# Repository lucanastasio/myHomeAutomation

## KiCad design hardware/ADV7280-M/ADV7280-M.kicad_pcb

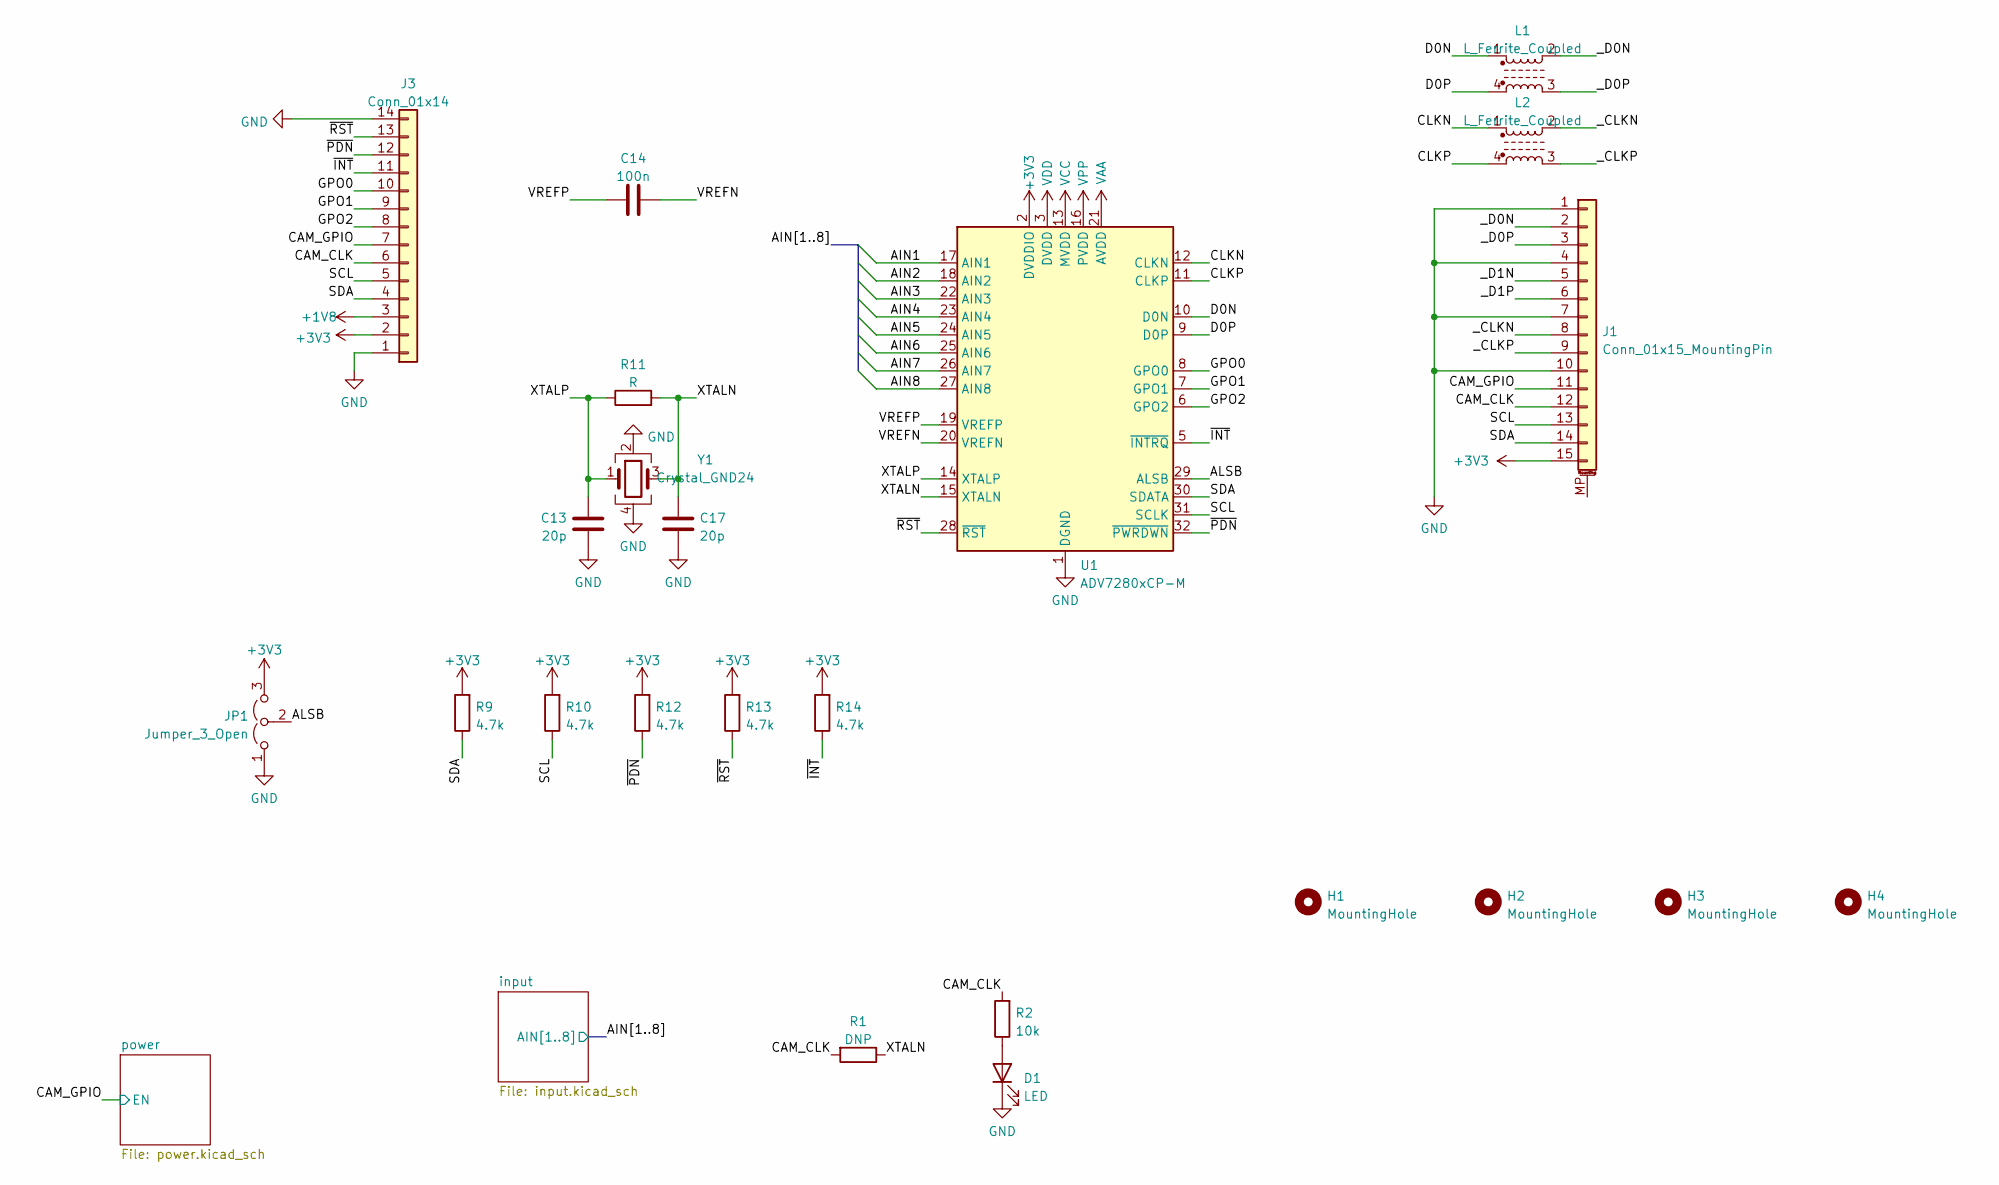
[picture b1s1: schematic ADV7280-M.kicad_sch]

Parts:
C13, C17: 20p; C_0402_1005Metric
C14: 100n; C_0402_1005Metric
D1: LED; LED_0603_1608Metric
H1, H2, H3, H4: MountingHole; MountingHole_2.7mm_M2.5
J1: Conn_01x15_MountingPin; TE_1-84952-5_1x15-1MP_P1.0mm_Horizontal
J3: Conn_01x14; PinHeader_1x14_P2.54mm_Vertical
JP1: Jumper_3_Open; PinHeader_1x03_P2.54mm_Vertical
L1, L2: L_Ferrite_Coupled; L_CommonModeChoke_Coilcraft_0603USB
R1: DNP; R_0603_1608Metric
R2: 10k; R_0603_1608Metric
R9, R10, R12, R13, R14: 4.7k; R_0603_1608Metric
R11: R; R_0402_1005Metric
U1: ADV7280xCP-M; LFCSP-32-1EP_5x5mm_P0.5mm_EP3.6x3.6mm
Y1: Crystal_GND24; Crystal_SMD_3225-4Pin_3.2x2.5mm

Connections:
+1V8: J3.3; also elsewhere on the board
+3V3: J1.15, J3.2, JP1.3 (B), R9.2, R10.2, R12.2, R13.2, R14.2, U1.2 (DVDDIO); also elsewhere on the board
/AIN1: U1.17 (AIN1); also elsewhere on the board
/AIN2: U1.18 (AIN2); also elsewhere on the board
/AIN3: U1.22 (AIN3); also elsewhere on the board
/AIN4: U1.23 (AIN4); also elsewhere on the board
/AIN5: U1.24 (AIN5); also elsewhere on the board
/AIN6: U1.25 (AIN6); also elsewhere on the board
/AIN7: U1.26 (AIN7); also elsewhere on the board
/AIN8: U1.27 (AIN8); also elsewhere on the board
/ALSB: JP1.2 (C), U1.29 (ALSB)
/CAM_CLK: J1.12, J3.6, R1.2, R2.2
/CAM_GPIO: J1.11, J3.7; also elsewhere on the board
/CLKN: L2.1, U1.12 (CLKN)
/CLKP: L2.4, U1.11 (CLKP)
/D0N: L1.1, U1.10 (D0N)
/D0P: L1.4, U1.9 (D0P)
/GPO0: J3.10, U1.8 (GPO0)
/GPO1: J3.9, U1.7 (GPO1)
/GPO2: J3.8, U1.6 (GPO2)
/SCL: J1.13, J3.5, R10.1, U1.31 (SCLK)
/SDA: J1.14, J3.4, R9.1, U1.30 (SDATA)
/VREFN: C14.2, U1.20 (VREFN)
/VREFP: C14.1, U1.19 (VREFP)
/XTALN: C17.2, R1.1, R11.2, U1.15 (XTALN), Y1.3
/XTALP: C13.2, R11.1, U1.14 (XTALP), Y1.1
/_CLKN: J1.8, L2.2
/_CLKP: J1.9, L2.3
/_D0N: J1.2, L1.2
/_D0P: J1.3, L1.3
/_D1N: J1.5
/_D1P: J1.6
/~INT: J3.11, R14.1, U1.5 (~INTRQ)
/~PDN: J3.12, R12.1, U1.32 (~PWRDWN)
/~RST: J3.13, R13.1, U1.28 (~RST)
GND: C13.1, C17.1, D1.1 (K), J1.1, J1.4, J1.7, J1.10, J3.1, J3.14, JP1.1 (A), U1.1 (DGND), U1.4 (DGND), U1.33 (DGND), Y1.2, Y1.4; also elsewhere on the board
unnamed: D1.2 (A), R2.1
VAA: U1.21 (AVDD); also elsewhere on the board
VCC: U1.13 (MVDD); also elsewhere on the board
VDD: U1.3 (DVDD); also elsewhere on the board
VPP: U1.16 (PVDD); also elsewhere on the board

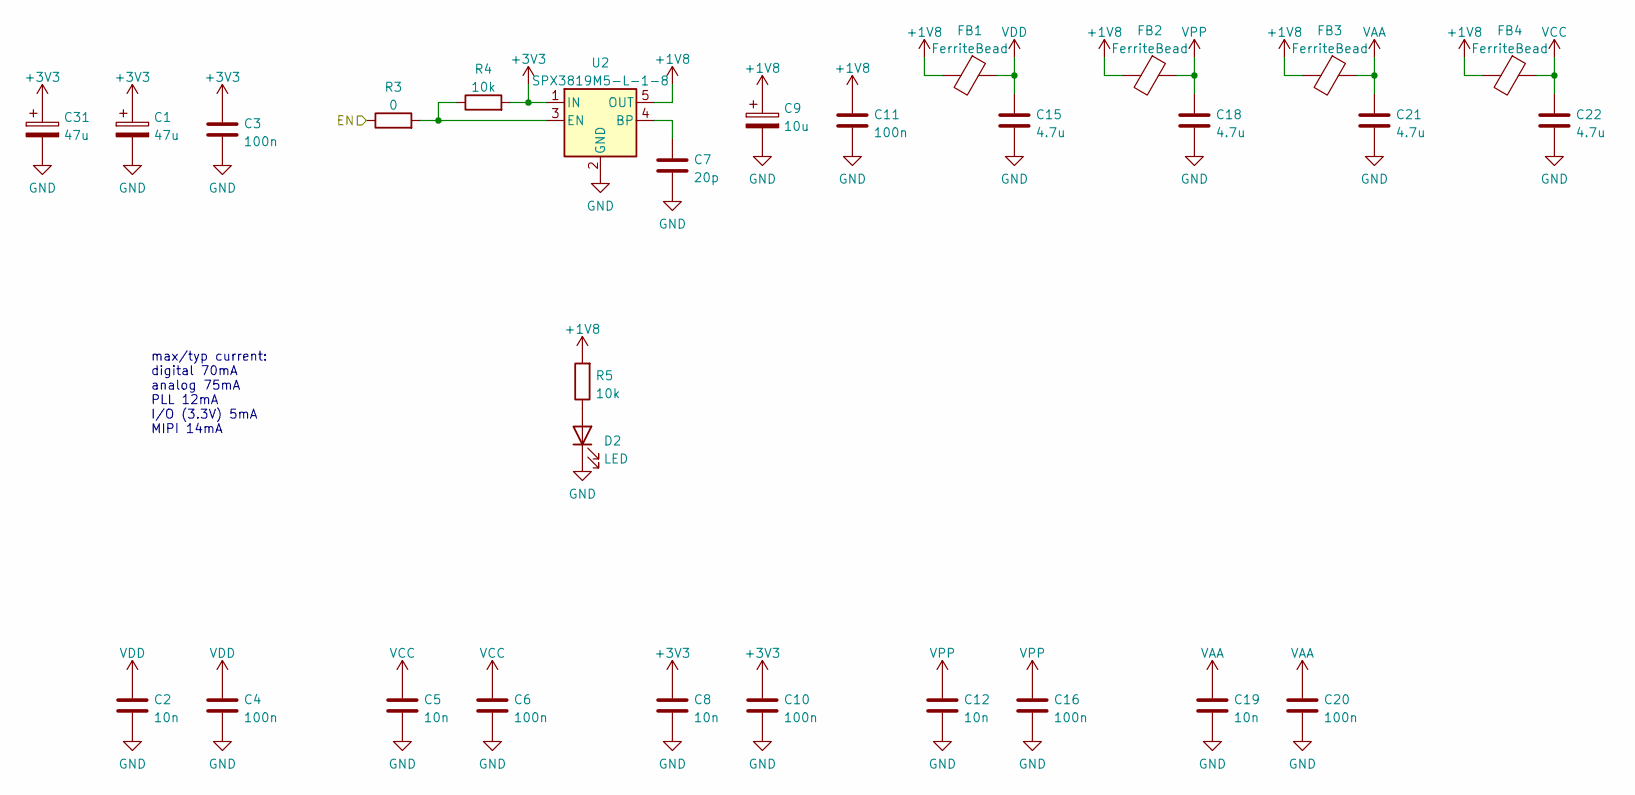
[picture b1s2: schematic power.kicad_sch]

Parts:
C1: 47u; CP_EIA-2012-15_AVX-P
C2, C5, C8, C12, C19: 10n; C_0402_1005Metric
C3, C11: 100n; C_0603_1608Metric
C4, C6, C10, C16, C20: 100n; C_0402_1005Metric
C7: 20p; C_0603_1608Metric
C9: 10u; CP_EIA-1608-08_AVX-J
C15, C18, C21, C22: 4.7u; C_0603_1608Metric
C31: 47u; CP_Radial_D6.3mm_P2.50mm
D2: LED; LED_0603_1608Metric
FB1, FB2, FB3, FB4: FerriteBead; L_0603_1608Metric
R3: 0; R_0603_1608Metric
R4, R5: 10k; R_0603_1608Metric
U2: SPX3819M5-L-1-8; SOT-23-5

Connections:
+1V8: C9.1, C11.2, FB1.2, FB2.2, FB3.2, FB4.2, R5.2, U2.5 (OUT); also elsewhere on the board
+3V3: C1.1, C3.2, C8.1, C10.1, C31.1, R4.2, U2.1 (IN); also elsewhere on the board
/CAM_GPIO: R3.1; also elsewhere on the board
GND: C1.2, C2.2, C3.1, C4.2, C5.2, C6.2, C7.1, C8.2, C9.2, C10.2, C11.1, C12.2, C15.1, C16.2, C18.1, C19.2, C20.2, C21.1, C22.1, C31.2, D2.1 (K), U2.2 (GND); also elsewhere on the board
unnamed: D2.2 (A), R5.1
unnamed: C7.2, U2.4 (BP)
unnamed: R3.2, R4.1, U2.3 (EN)
VAA: C19.1, C20.1, C21.2, FB3.1; also elsewhere on the board
VCC: C5.1, C6.1, C22.2, FB4.1; also elsewhere on the board
VDD: C2.1, C4.1, C15.2, FB1.1; also elsewhere on the board
VPP: C12.1, C16.1, C18.2, FB2.1; also elsewhere on the board

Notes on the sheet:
max/typ current: digital 70mA analog 75mA PLL 12mA I/O (3.3V) 5mA MIPI 14mA

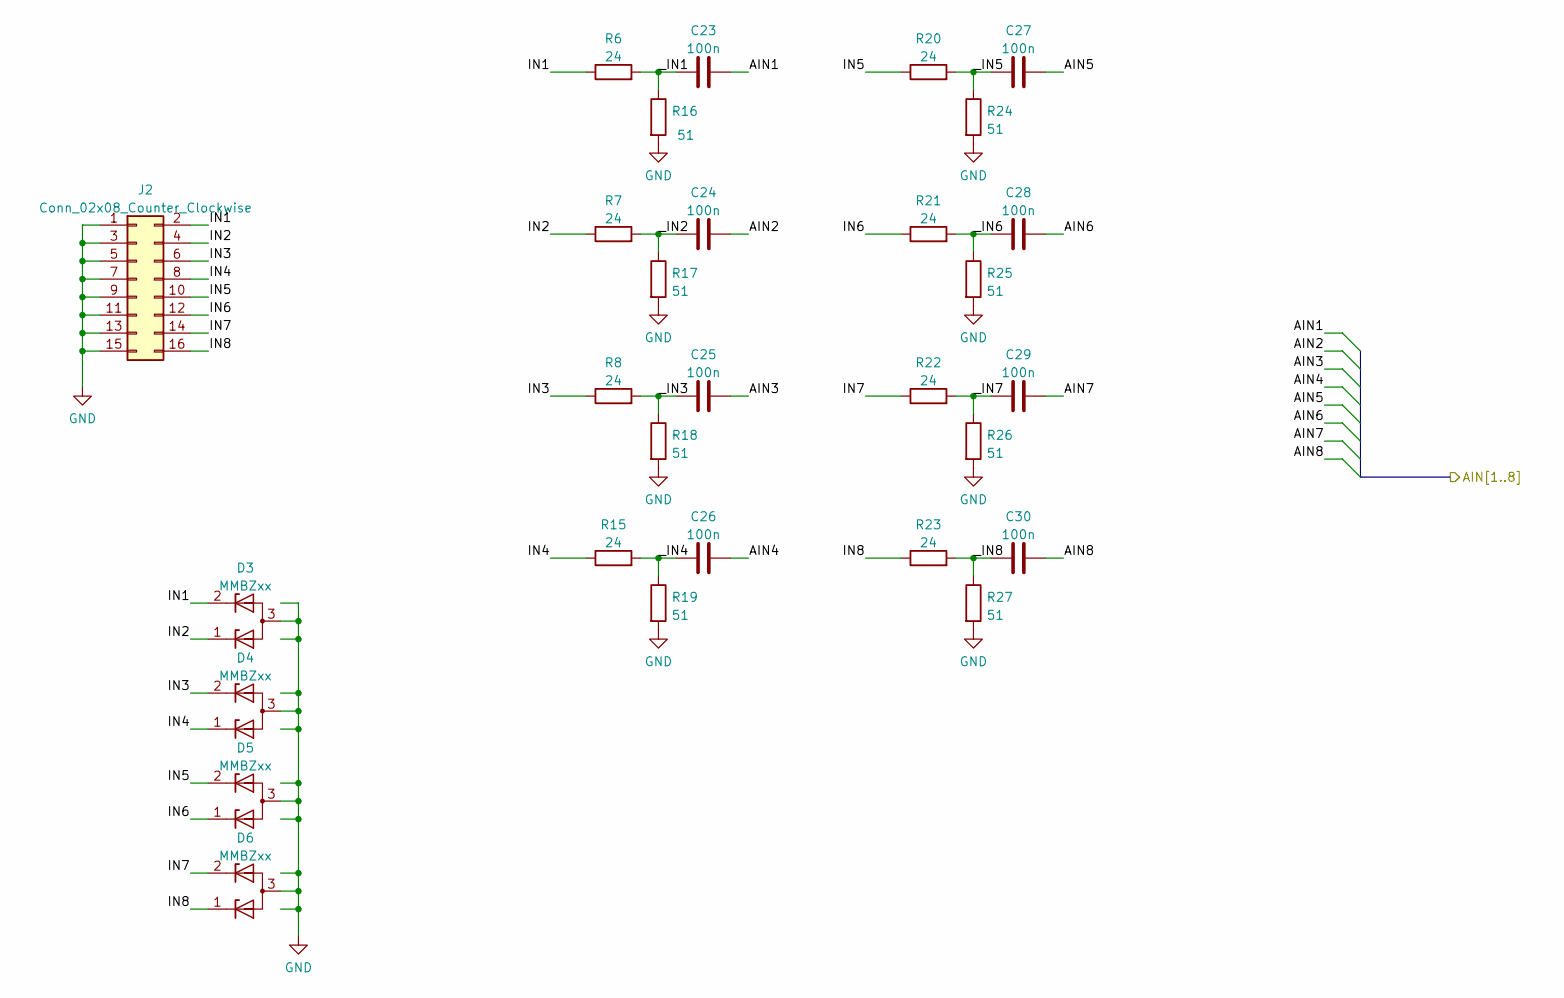
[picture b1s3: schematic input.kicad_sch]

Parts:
C23, C24, C25, C26, C27, C28, C29, C30: 100n; C_0603_1608Metric
D3, D4, D5, D6: MMBZxx; SOT-23
J2: Conn_02x08_Counter_Clockwise; PinHeader_2x08_P2.54mm_Vertical
R6, R7, R8, R15, R20, R21, R22, R23: 24; R_0603_1608Metric
R16, R17, R18, R19, R24, R25, R26, R27: 51; R_0603_1608Metric

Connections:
/AIN1: C23.2; also elsewhere on the board
/AIN2: C24.2; also elsewhere on the board
/AIN3: C25.2; also elsewhere on the board
/AIN4: C26.2; also elsewhere on the board
/AIN5: C27.2; also elsewhere on the board
/AIN6: C28.2; also elsewhere on the board
/AIN7: C29.2; also elsewhere on the board
/AIN8: C30.2; also elsewhere on the board
/input/IN1: D3.2 (K), J2.2, R6.1
/input/IN2: D3.1 (K), J2.4, R7.1
/input/IN3: D4.2 (K), J2.6, R8.1
/input/IN4: D4.1 (K), J2.8, R15.1
/input/IN5: D5.2 (K), J2.10, R20.1
/input/IN6: D5.1 (K), J2.12, R21.1
/input/IN7: D6.2 (K), J2.14, R22.1
/input/IN8: D6.1 (K), J2.16, R23.1
/input/_IN1: C23.1, R6.2, R16.1
/input/_IN2: C24.1, R7.2, R17.1
/input/_IN3: C25.1, R8.2, R18.1
/input/_IN4: C26.1, R15.2, R19.1
/input/_IN5: C27.1, R20.2, R24.1
/input/_IN6: C28.1, R21.2, R25.1
/input/_IN7: C29.1, R22.2, R26.1
/input/_IN8: C30.1, R23.2, R27.1
GND: D3.3 (A), D4.3 (A), D5.3 (A), D6.3 (A), J2.1, J2.3, J2.5, J2.7, J2.9, J2.11, J2.13, J2.15, R16.2, R17.2, R18.2, R19.2, R24.2, R25.2, R26.2, R27.2; also elsewhere on the board

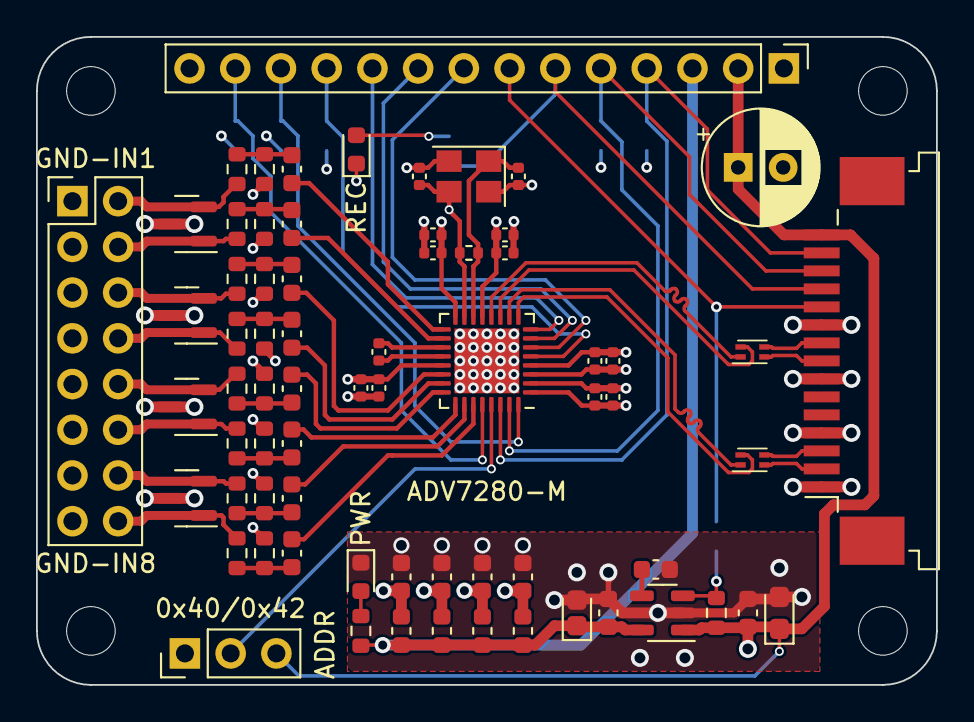
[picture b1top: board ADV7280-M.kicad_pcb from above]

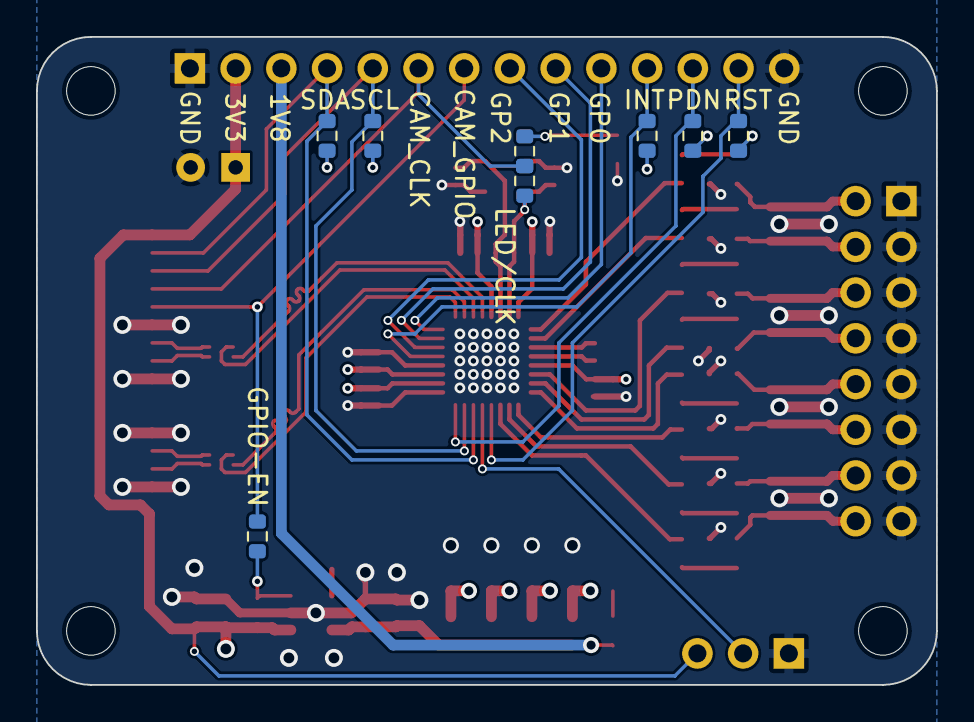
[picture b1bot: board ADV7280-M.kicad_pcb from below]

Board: 4 copper layers, 50.0 x 36.0 mm, 81 parts (8 on the bottom side), 58 nets.

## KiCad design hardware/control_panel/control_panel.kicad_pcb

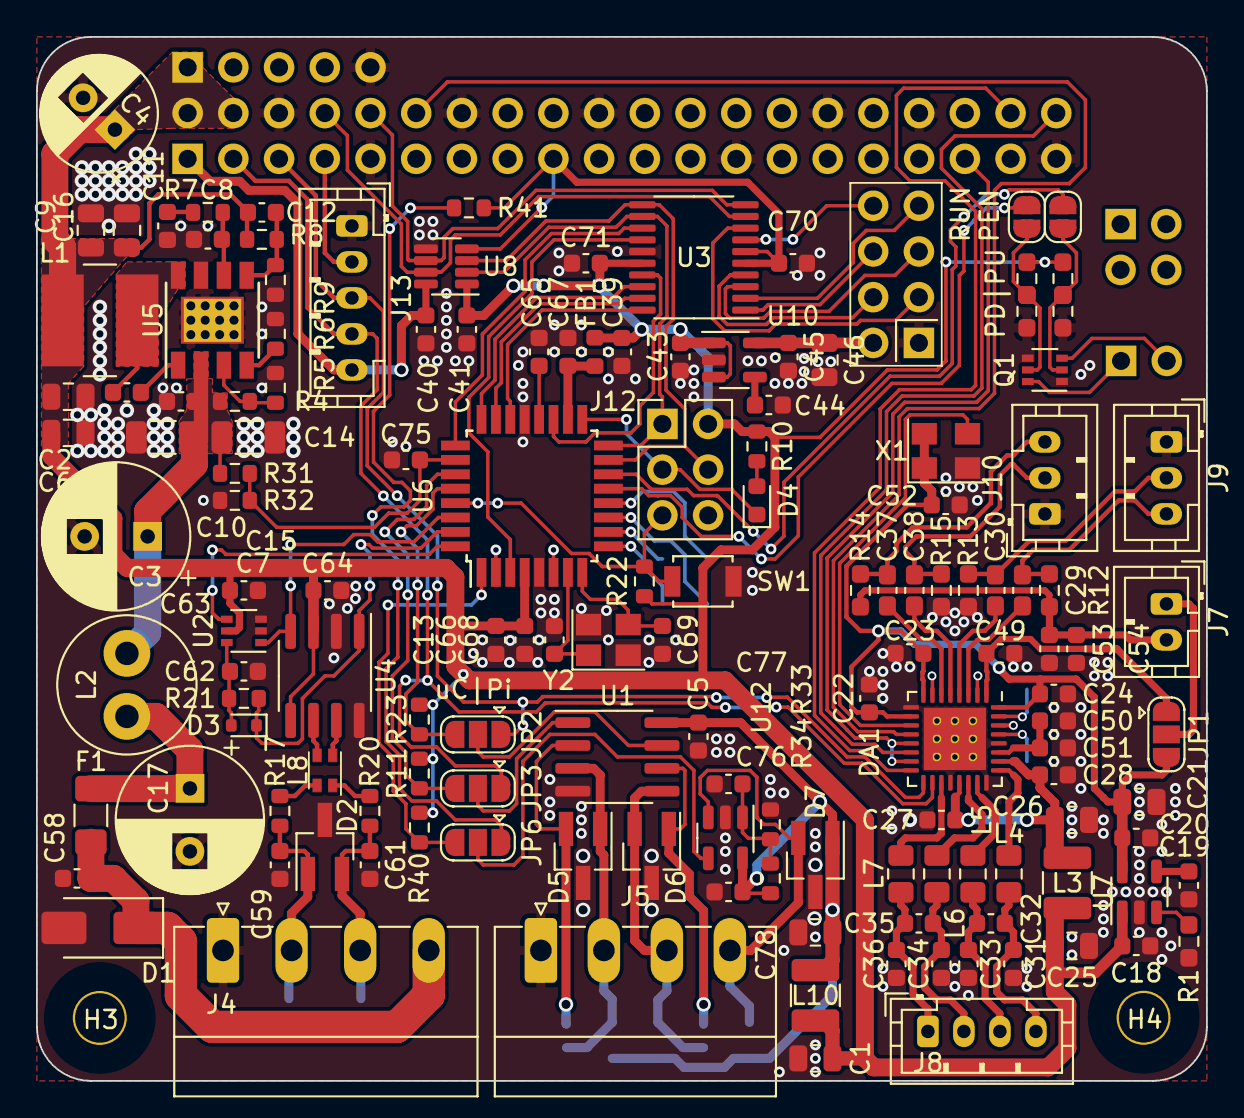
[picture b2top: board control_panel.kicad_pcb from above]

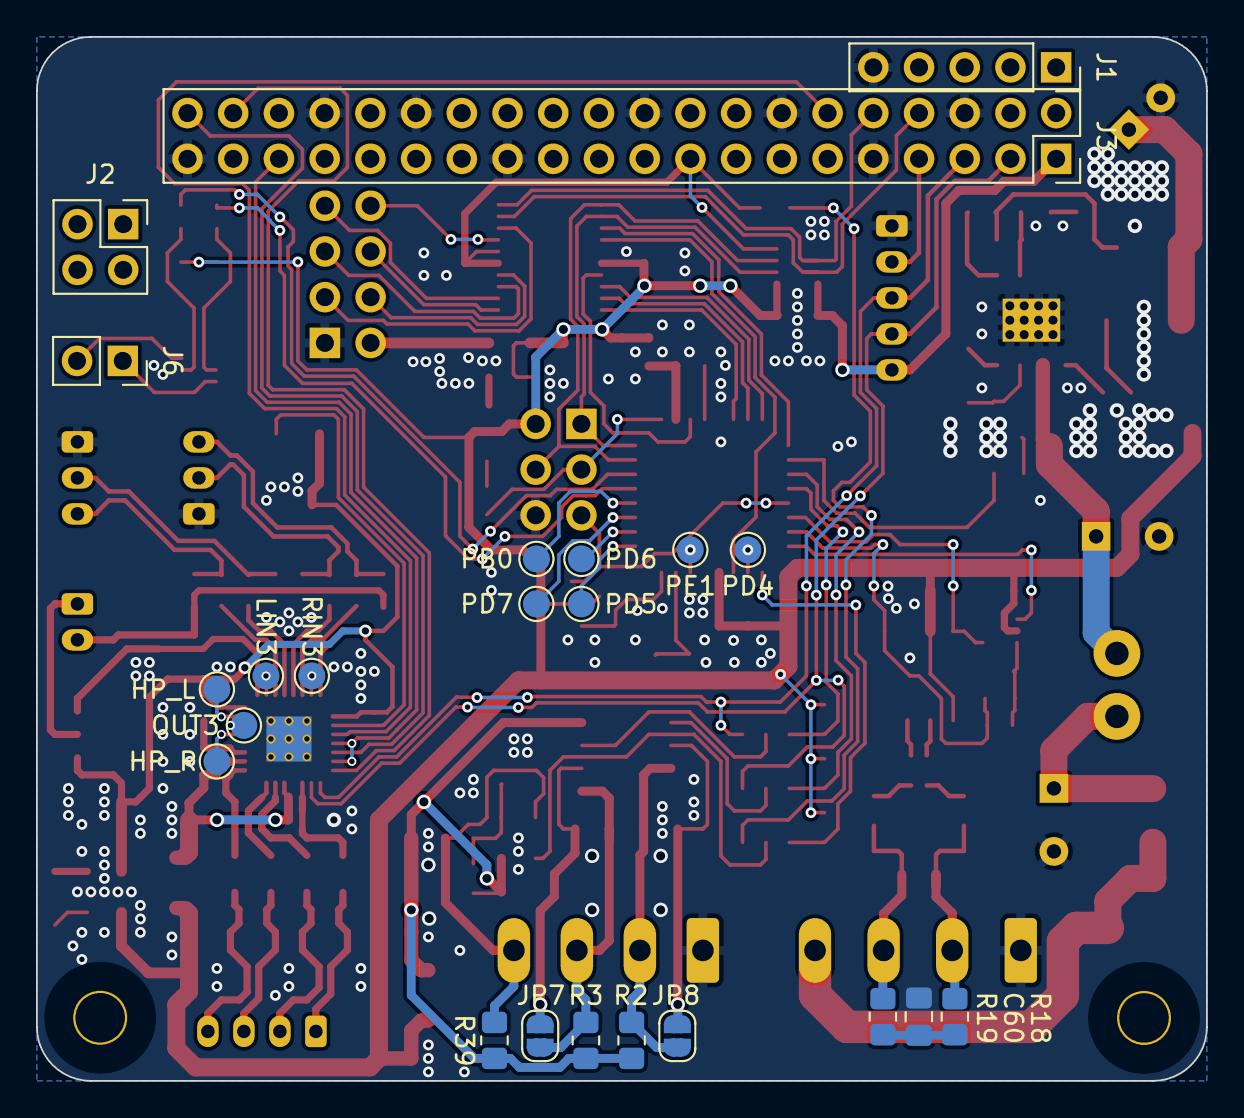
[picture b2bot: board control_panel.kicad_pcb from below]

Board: 2 copper layers, 65.0 x 58.0 mm, 169 parts (23 on the bottom side), 113 nets.

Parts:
C1, C2, C6, C9, C16, C21, C25, C26, C46, C78: 22u; C_0805_2012Metric
C3, C17: 100u_50V; CP_Radial_D8.0mm_P3.50mm
C4: 220u_16V; CP_Radial_D6.3mm_P2.50mm
C5, C40, C41, C54, C64, C65, C66, C67, C70, C71, C75, C76, C77: 100n; C_0603_1608Metric
C7, C14: 10u; C_1206_3216Metric
C8, C10, C11, C12, C15, C31, C32, C33, C34, C35, C36, C58, C59, C61, C62, C63: C; C_0603_1608Metric
C13, C18, C20, C22, C23, C24, C27, C28, C39, C43, C45, C49, C51, C52: 1u; C_0603_1608Metric
C19, C44: 22n; C_0603_1608Metric
C29, C30, C37, C38: C; C_0603_1608Metric_Pad1.08x0.95mm_HandSolder
C50, C53: 4.7u; C_0603_1608Metric
C60: C; C_0805_2012Metric_Pad1.18x1.45mm_HandSolder
C68, C69: 20p; C_0603_1608Metric
D1: D_Zener; D_SMA
D2: SM712_SOT23; SOT-23_Handsoldering
D3: DNP; D_SOD-523
D4: LED; LED_0603_1608Metric
D5, D6, D7: D; SOT-23_Handsoldering
DA1: WM8960; QFN-32-1EP_5x5mm_P0.5mm_EP3.45x3.45mm_ThermalVias
F1: Fuse; Fuse_1206_3216Metric_Pad1.42x1.75mm_HandSolder
FB1: FerriteBead; L_0603_1608Metric
H3, H4: 3mm_Mounting_Hole; NPTH_3mm_ID
J1: display; PinSocket_1x05_P2.54mm_Vertical
J2: Conn_02x02_Odd_Even; PinSocket_2x02_P2.54mm_Vertical
J3: 40HAT; raspberry_pi
J4: Screw_Terminal_CAN; PhoenixContact_MC_1,5_4-G-3.81_1x04_P3.81mm_Horizontal
J5: Screw_Terminal_01x04; PhoenixContact_MC_1,5_4-G-3.5_1x04_P3.50mm_Horizontal
J6: Conn_01x02; PinSocket_1x02_P2.54mm_Vertical
J7: Conn_01x02; JST_PH_B2B-PH-K_1x02_P2.00mm_Vertical
J8: Conn_01x04; JST_PH_B4B-PH-K_1x04_P2.00mm_Vertical
J9, J10: Conn_01x03; JST_PH_B3B-PH-K_1x03_P2.00mm_Vertical
J12: AVR-ISP-6; PinHeader_2x03_P2.54mm_Vertical
J13: motion and brightness sensors; JST_PH_B5B-PH-K_1x05_P2.00mm_Vertical
JP1, JP2, JP3, JP6: SolderJumper_3_Open; SolderJumper-3_P1.3mm_Open_RoundedPad1.0x1.5mm
JP4, JP5, JP7, JP8: SolderJumper_2_Open; SolderJumper-2_P1.3mm_Open_RoundedPad1.0x1.5mm
L1: 47u_3A; L_Bourns-SRN6045
L2: L_Ferrite; L_Radial_D7.5mm_P3.50mm_Fastron_07P
L3, L10: L; L_1210_3225Metric
L4, L5, L6, L7: L; L_0805_2012Metric_Pad1.15x1.40mm_HandSolder
L8: L_Ferrite_Coupled; L_CommonModeChoke_Coilcraft_0805USB
Q1: 2N7002DW; SOT-363_SC-70-6
R1, R12, R13, R14, R15, R27, R28, R29, R30: R; R_0603_1608Metric_Pad0.98x0.95mm_HandSolder
R2, R3, R39: 200; R_0805_2012Metric_Pad1.20x1.40mm_HandSolder
R4, R5, R6, R7, R8, R9, R10, R11, R17, R20, R22, R23, R40, R41: R; R_0603_1608Metric
R18, R19: R; R_0805_2012Metric_Pad1.20x1.40mm_HandSolder
R21: 0; R_0603_1608Metric
R31: 470k; R_0603_1608Metric
R32: 12k; R_0603_1608Metric
R33, R34: 100k; R_0603_1608Metric
SW1: SW_Push; SW_SPST_B3U-1000P
TP1: PB0; TestPoint_Pad_D1.5mm
TP2: PD4; TestPoint_Pad_D1.5mm
TP3: PD5; TestPoint_Pad_D1.5mm
TP4: PD6; TestPoint_Pad_D1.5mm
TP5: PD7; TestPoint_Pad_D1.5mm
TP6: PE1; TestPoint_Pad_D1.5mm
TP7: HP_R; TestPoint_Pad_D1.5mm
TP8: OUT3; TestPoint_Pad_D1.5mm
TP9: HP_L; TestPoint_Pad_D1.5mm
TP10: LIN3; TestPoint_Pad_D1.5mm
TP11: RIN3; TestPoint_Pad_D1.5mm
U1: P82B96; SOIC-8_3.9x4.9mm_P1.27mm
U2: 74LVC1G57; SOT-363_SC-70-6
U3: TXB0108DQSR; TSSOP-20_4.4x6.5mm_P0.65mm
U4: TJA1051T-3; SOIC-8_3.9x4.9mm_P1.27mm
U5: AP64352; Diodes_SO-8EP
U6: ATmega328PB-A; TQFP-32_7x7mm_P0.8mm
U7, U10: SPX3819M5-L-3-3; SOT-23-5
U8: BCT0102; SOT-23-8
U9: NRF24L01_Breakout; nRF24L01_Breakout
U12: LM397; SOT-23-5
X1: SG-8002CE; Oscillator_SMD_SeikoEpson_SG8002CE-4Pin_3.2x2.5mm
Y2: Crystal_GND24; Crystal_SMD_3225-4Pin_3.2x2.5mm

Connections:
+3.3V: C40.2, C70.2, J3.1 (P3V3), J3.17 (P3V3), J13.5, R41.1, U3.5 (VCCA), U3.6 (OE), U8.4 (OE), U8.8 (VCCA)
+3.3VA: C20.1, C21.1, C22.1, C23.1, C24.1, C52.1, DA1.8 (DCVDD), DA1.10 (DBVDD), DA1.32 (AVDD), JP1.3 (B), U7.5 (OUT), X1.1 (OE), X1.4 (Vcc)
+5V: C1.1, C2.1, C4.1, C6.1, C9.1, C12.2, C13.2, C16.1, C18.1, C25.1, C39.2, C41.2, C43.1, C63.1, C64.2, C66.2, C71.2, FB1.1, J1.1, J3.2 (P5V), J3.4 (P5V), J12.2 (VCC), L1.2, L3.1, L10.1, R8.1, R10.1, R11.1, R22.1, R23.1, R27.1, R28.1, R40.1, U2.5 (VCC), U3.16 (VCCB), U4.3 (VCC), U4.5 (VIO), U6.4 (VCC), U7.1 (IN), U8.1 (VCCB), U10.1 (IN), U10.3 (EN)
+5VA: C67.1, FB1.2, U6.18 (AVCC)
+5VD: C5.1, C76.1, C78.1, D7.1 (A1), L10.2, R2.1, R3.1, R34.1, R39.1, U1.8 (VCC), U12.5 (V+)
+24V: C3.1, C7.1, C14.1, C15.2, L2.2, R4.1, R31.1, U5.2 (VIN)
/ADC: DA1.16 (ADCDAT), J3.38 (BCM20)
/A_EN: R1.1, U7.3 (EN)
/BUS_CD: U2.4 (Y), U6.32 (PD2)
/BUS_RX: U2.1 (IN1), U4.4 (RXD), U6.30 (PD0)
/BUS_TX: D3.1 (K), R21.2, U4.1 (TXD), U6.31 (PD1)
/CAN/CAN_{Hin}: C61.1, D2.2 (A2), J4.3, R19.2, R20.1
/CAN/CAN_{H}: L8.2, U4.7 (CANH)
/CAN/CAN_{Lin}: C59.1, D2.1 (A1), J4.2, R17.1, R18.1
/CAN/CAN_{L}: L8.3, U4.6 (CANL)
/CAN/CAN_{SPLIT}: C60.1, R18.2, R19.1
/CAN/TX_{DL}: C62.1, D3.2 (A), R21.1, U2.6 (IN2)
/CAN/Vin: C58.1, D1.1 (K), F1.1, J4.4
/CLK: DA1.12 (BCLK), J3.12 (BCM18)
/DAC: DA1.14 (DACDAT), J3.40 (BCM21)
/EXT.SCL: JP2.2 (C), U1.7 (SCL)
/EXT.SDA: JP3.2 (C), U1.1 (SDA)
/GW_RX: J12.1 (MISO), U3.12 (B7), U6.16 (PB4), U8.2 (B1)
/GW_TX: J12.4 (MOSI), U3.11 (B8), U6.15 (PB3), U8.3 (B2)
/I2C/INT: D7.2 (A2), J5.4, R39.2, U12.3 (+)
/I2C/INT_REF: C77.1, R33.1, R34.2, U12.1 (-)
/I2C/SCL_{R}: D6.1 (A1), JP7.1 (A), U1.6 (RXD-SCL)
/I2C/SCL_{T}: D6.2 (A2), J5.3, JP7.2 (B), R3.2, U1.5 (TXD-SCL)
/I2C/SDA_{R}: D5.2 (A2), JP8.1 (A), U1.2 (RXD-SDA)
/I2C/SDA_{T}: D5.1 (A1), J5.2, JP8.2 (B), R2.2, U1.3 (TXD-SDA)
/LRC: DA1.13 (DACLRC), DA1.15 (ADCLRC/GPIO1), J3.35 (BCM19)
/MCU/AREF: C65.1, U6.20 (AREF)
/MCU/ISP_SCK: D4.1 (K), J12.3 (SCK), U6.17 (PB5)
/MCU/PEN: JP4.1 (A), U6.14 (PB2)
/MCU/RUN: JP5.1 (A), U6.13 (PB1)
/MCU/VSEN: C75.2, R31.2, R32.1, U6.26 (PC3)
/MCU/XTAL1: C68.1, U6.7 (XTAL1/PB6), Y2.1
/MCU/XTAL2: C69.1, U6.8 (XTAL2/PB7), Y2.3
/MCU/~ISP_RST: J12.5 (~RST), R22.2, SW1.1, U6.29 (~RESET/PC6)
/MOT: J3.7 (BCM4), J13.2
/PI_INT: JP6.1 (A), R41.2
/PI_PEN: J6.1, Q1.6 (D)
/PI_RUN: J6.2, Q1.3 (D)
/PI_RX: J3.10 (BCM15), U3.10 (A8), U8.6 (A2)
/PI_TX: J3.8 (BCM14), U3.9 (A7), U8.7 (A1)
/RF.CE: U3.8 (A6), U9.3 (CE)
/RF.CSN: U3.4 (A4), U9.4 (~CSN)
/RF.IRQ: U3.7 (A5), U9.8 (IRQ)
/RF.MISO: U3.2 (A2), U9.7 (MISO)
/RF.MOSI: U3.1 (A1), U9.6 (MOSI)
/RF.SCK: U3.3 (A3), U9.5 (SCK)
/SCL: DA1.17 (SCLK), J3.5 (BCM3), J13.3, JP2.1 (A)
/SDA: DA1.18 (SDIN), J3.3 (BCM2), J13.4, JP3.1 (A)
/UC.CE: U3.13 (B6), U6.25 (PC2)
/UC.CSN: U3.17 (B4), U6.19 (PE2)
/UC.IRQ: U3.14 (B5), U6.3 (PE0)
/UC.MISO: U3.19 (B2), U6.23 (PC0)
/UC.MOSI: U3.20 (B1), U6.22 (PE3)
/UC.SCK: U3.18 (B3), U6.24 (PC1)
/UC.SCL: JP2.3 (B), R23.2, U6.28 (PC5)
/UC.SDA: JP3.3 (B), R11.2, U6.27 (PC4)
/UC_INT: JP6.3 (B), R40.2, U6.1 (PD3)
/Vreg/BST: C10.1, U5.1 (BST)
/Vreg/EN: R4.2, R5.1, U5.3 (EN)
/Vreg/FB: C12.1, R8.2, R9.1, U5.5 (FB)
/Vreg/RT: R6.1, U5.4 (RT/CLK)
/Vreg/SS: C8.1, R7.1, U5.6 (SS)
/Vreg/SW: C10.2, L1.1, U5.8 (SW)
/Vreg/~SS: C11.1, R7.2
/audio/BP: C19.1, U7.4 (BP)
/audio/HP_L: DA1.31 (HP_L), TP9.1
/audio/HP_R: DA1.29 (HP_R), TP7.1
/audio/INL+: C29.2, J9.3, R12.2
/audio/INL-: C30.2, J9.2, R13.1
/audio/INR+: C37.2, J10.3, R14.2
/audio/INR-: C38.2, J10.2, R15.1
/audio/LIN3: DA1.2 (LINPUT3/JD2), TP10.1
/audio/LIN+: C29.1, DA1.3 (LINPUT2)
/audio/LIN-: C30.1, DA1.4 (LINPUT1)
/audio/MCLK: DA1.11 (MCLK), X1.3 (OUT)
/audio/MICBIAS: C49.1, DA1.1 (MICBIAS), JP1.1 (A)
/audio/OUT3: DA1.30 (OUT3), TP8.1
/audio/RIN3: DA1.7 (RINPUT3/JD3), TP11.1
/audio/RIN+: C37.1, DA1.6 (RINPUT2)
/audio/RIN-: C38.1, DA1.5 (RINPUT1)
/audio/SPK_LN: DA1.23 (SPK_LN), L5.1
/audio/SPK_LP: DA1.25 (SPK_LP), L4.1
/audio/SPK_RN: DA1.19 (SPK_RN), L7.1
/audio/SPK_RP: DA1.22 (SPK_RP), L6.1
/audio/SPL+: C31.2, C32.1, J8.4, L4.2
/audio/SPL-: C32.2, C33.1, J8.3, L5.2
/audio/SPR+: C34.2, C35.1, J8.2, L6.2
/audio/SPR-: C35.2, C36.1, J8.1, L7.2
/audio/VMIC: C53.1, C54.1, J7.2, R12.1, R14.1
/audio/VMID: C50.1, C51.1, DA1.27 (VMID)
/audio/VSPK: C26.1, C27.1, C28.1, DA1.21 (SPKVDD2), DA1.26 (SPKVDD1), L3.2
/nrf24/3V3_RF: C45.1, C46.1, U9.2 (VCC), U10.5 (OUT)
/nrf24/BP: C44.1, U10.4 (BP)
/~INT: JP6.2 (C), U12.4
GND: C1.2, C2.2, C3.2, C4.2, C5.2, C6.2, C7.2, C8.2, C9.2, C11.2, C13.1, C14.2, C15.1, C16.2, C17.2, C18.2, C19.2, C20.2, C21.2, C22.2, C23.2, C24.2, C25.2, C26.2, C27.2, C28.2, C31.1, C33.2, C34.1, C36.2, C39.1, C40.1, C41.1, C43.2, C44.2, C45.2, C46.2, C49.2, C50.2, C51.2, C52.2, C53.2, C54.2, C58.2, C59.2, C60.2, C61.2, C62.2, C63.2, C64.1, C65.2, C66.1, C67.2, C68.2, C69.2, C70.1, C71.1, C75.1, C76.2, C77.2, C78.2, D1.2 (A), D2.3 (common), D5.3 (common), D6.3 (common), D7.3 (common), DA1.9 (DGND), DA1.20 (SPKGND2), DA1.24 (SPKGND1), DA1.28 (AGND), DA1.33 (GND), J1.5, J3.6 (GND), J3.9 (GND), J3.14 (GND), J3.20 (GND), J3.25 (GND), J3.30 (GND), J3.34 (GND), J3.39 (GND), J4.1, J5.1, J9.1, J10.1, J12.6 (GND), J13.1, Q1.1 (S), Q1.4 (S), R1.2, R5.2, R6.2, R9.2, R13.2, R15.2, R29.2, R30.2, R32.2, R33.2, SW1.2, U1.4 (GND), U2.2 (GND), U2.3 (IN0), U3.15 (GND), U4.2 (GND), U4.8 (S), U5.7 (GND), U5.9 (EP), U6.5 (GND), U6.21 (GND), U7.2 (GND), U8.5 (GND), U9.1 (GND), U10.2 (GND), U12.2 (V-), X1.2 (GND), Y2.2, Y2.4
unnamed: D4.2 (A), R10.2
unnamed: J7.1, JP1.2 (C)
unnamed: JP4.2 (B), Q1.2 (G), R28.2, R29.1
unnamed: JP5.2 (B), Q1.5 (G), R27.2, R30.1
unnamed: L8.1, R20.2
unnamed: L8.4, R17.2
unnamed: TP1.1, U6.12 (PB0)
unnamed: TP2.1, U6.2 (PD4)
unnamed: TP3.1, U6.9 (PD5)
unnamed: TP4.1, U6.10 (PD6)
unnamed: TP5.1, U6.11 (PD7)
unnamed: TP6.1, U6.6 (PE1)
VBUS: C17.1, F1.2, L2.1
